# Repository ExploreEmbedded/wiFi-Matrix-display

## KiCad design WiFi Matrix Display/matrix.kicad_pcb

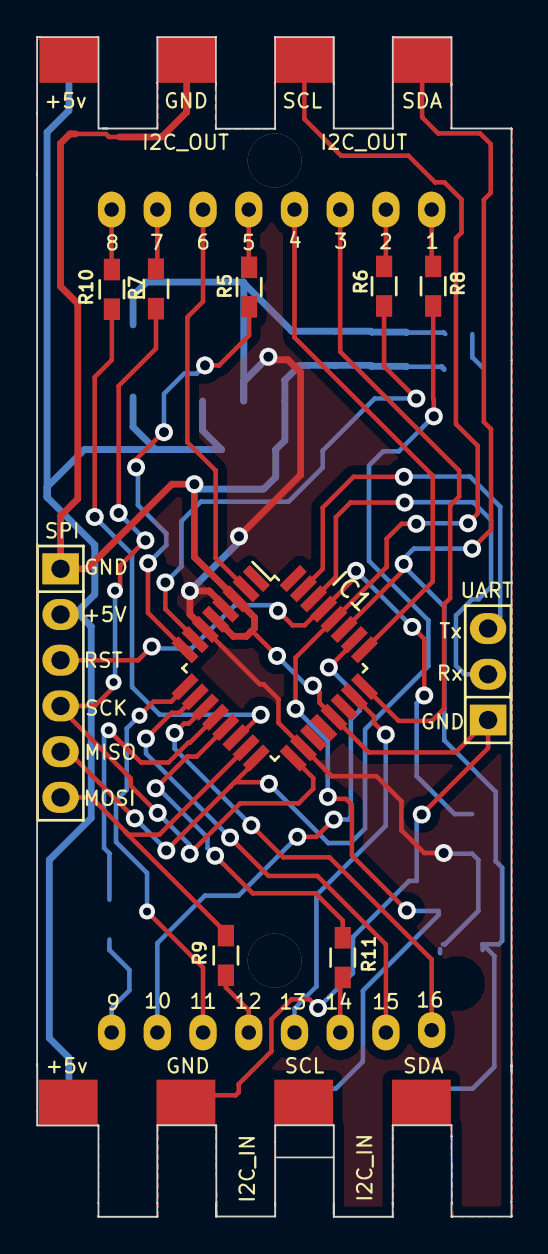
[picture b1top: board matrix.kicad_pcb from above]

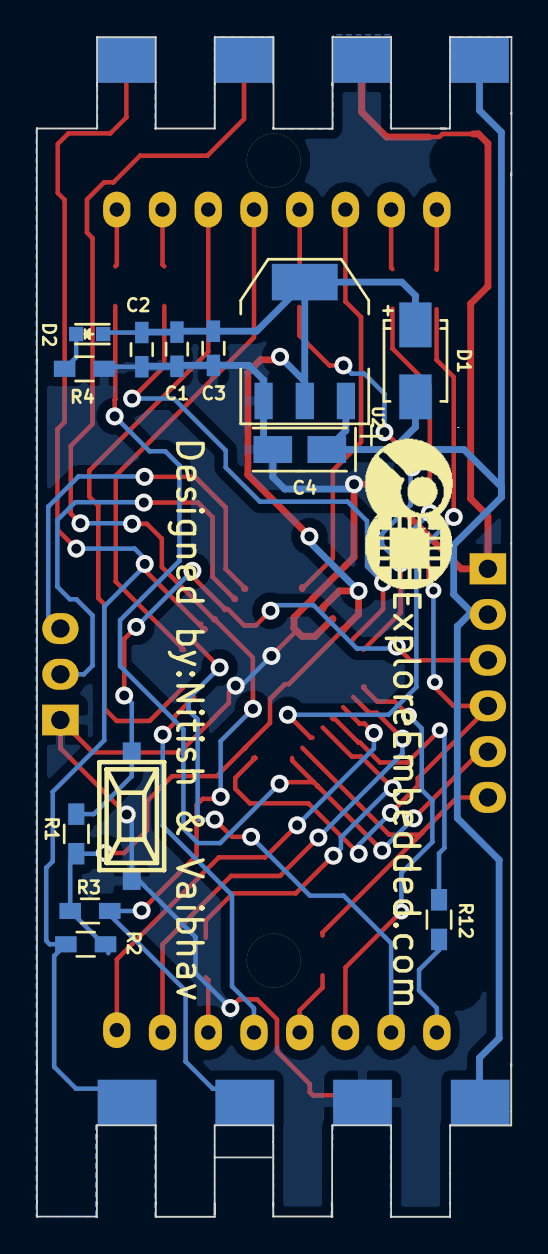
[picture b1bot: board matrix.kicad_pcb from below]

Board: 2 copper layers, 26.4 x 65.6 mm, 29 parts (14 on the bottom side), 33 nets.

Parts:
C1, C2, C3: 0.1uf; C_0603_HandSoldering
C4: 10uF; TantalC_SizeA_EIA-3216_Wave
D1: DIODE; SMA_Standard
D2: LED; LED-0603
IC1: ATMEGA8-AI; TQFP-32_7x7mm_Pitch0.8mm
LOGO: LOGO (2)
P1: CONN_01X06; Pin_Header_Straight_1x06
P2, P3: CONN_01X04; matrix_connector
P4: CONN_01X03; Pin_Header_Straight_1x03
P5, P6: CONN_01X01; 1pin
R1, R2, R3: 10K; R_0603_HandSoldering
R4: 470E; R_0603_HandSoldering
R5, R6, R7, R8, R9, R10, R11, R12: 22E; R_0603_HandSoldering
SW1: SPST; smd_push
U1: DispHB2388; 8x8dot matrix
U2: lm1117/3.3; lm117_SOT-223

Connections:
+3V3: C1.1, C2.1, C3.1, D1.1, D2.1, IC1.4, IC1.6, IC1.18, R1.1, R2.1, R3.1, U2.2, U2.4
+5V: C4.1, D1.2, P1.2, P2.1, P3.1, U2.3
/MISO: IC1.16, P1.5, R8.1
/MOSI: IC1.15, P1.6, R9.1
/PB6: IC1.7, R6.1
/PB7: IC1.8, R5.1
/RST: IC1.29, P1.3, R1.2, SW1.2
/Rx: IC1.30, P4.2
/SCK: IC1.17, P1.4, R7.1
/SCL: IC1.28, P2.3, P3.3, R3.2
/SDA: IC1.27, P2.4, P3.4, R2.2
/Tx: IC1.31, P4.3
GND: C1.2, C2.2, C3.2, C4.2, IC1.3, IC1.5, IC1.21, P1.1, P2.2, P3.2, P4.1, R4.2, SW1.1, U2.1
unnamed: D2.2, R4.1
unnamed: IC1.2, U1.6
unnamed: IC1.9, U1.11
unnamed: IC1.10, U1.15
unnamed: IC1.11, U1.16
unnamed: IC1.12, R12.1
unnamed: IC1.13, R11.1
unnamed: IC1.14, R10.1
unnamed: IC1.23, U1.13
unnamed: IC1.24, U1.3
unnamed: IC1.25, U1.4
unnamed: IC1.26, U1.10
unnamed: R5.2, U1.5
unnamed: R6.2, U1.2
unnamed: R7.2, U1.7
unnamed: R8.2, U1.1
unnamed: R9.2, U1.12
unnamed: R10.2, U1.8
unnamed: R11.2, U1.14
unnamed: R12.2, U1.9

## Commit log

2015-10-29 Hardware design files
